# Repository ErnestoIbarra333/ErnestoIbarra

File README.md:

This are some of my school projects and personal projects :)

Metal_Friends: https://ernestoibarra333.github.io/projects/

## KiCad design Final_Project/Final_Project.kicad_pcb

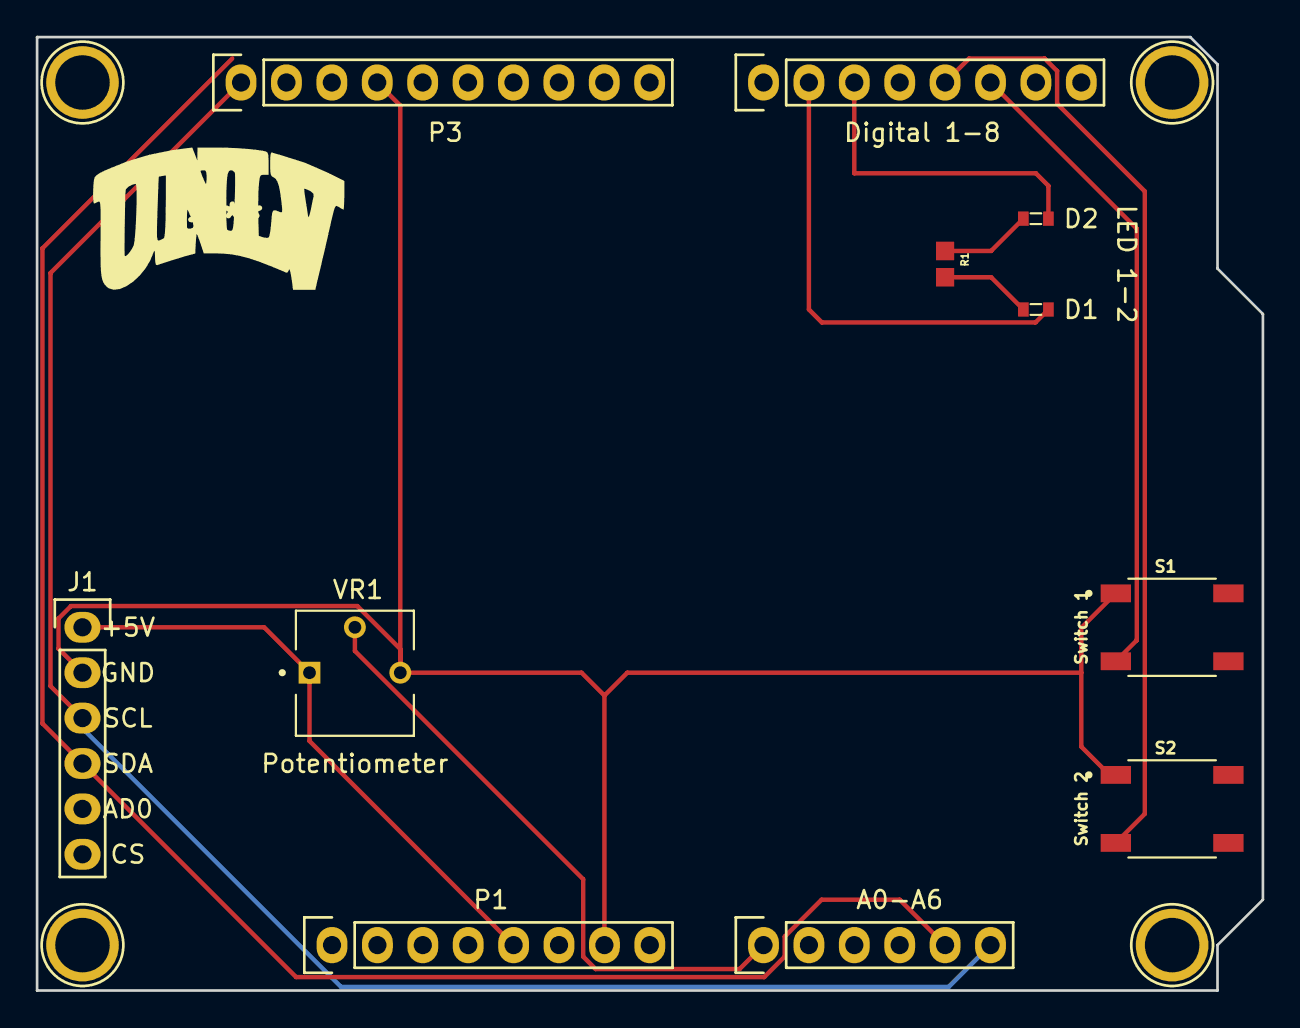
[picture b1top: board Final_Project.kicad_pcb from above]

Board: 2 copper layers, 68.6 x 53.3 mm, 15 parts (0 on the bottom side), 11 nets.

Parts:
A0-A6: Analog; Socket_Strip_Arduino_1x06
D1, D2: LTST-C193TBKT-5A; 0603
Digital 1-8: Digital; Socket_Strip_Arduino_1x08
J1: Conn_01x06_Female; Socket_Strip_Arduino_1x06
P1: Power; Socket_Strip_Arduino_1x08
P3: Digital; Socket_Strip_Arduino_1x10
P5, P6, P6#2, P8: CONN_01X01; Arduino_1pin
R1: RC0603JR-071KL; RESC1607X60N
S1, S2: 8-1437565-1; SW_8-1437565-1
VR1: 3362P-1-103LF; TRIM_3362P-1-103LF

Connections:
+5V: J1.1, P1.5, VR1.1
/2: Digital 1-8.6, S1.3
/3(**): Digital 1-8.5, S2.3
/5(**): D2.2, Digital 1-8.3
/6(**): D1.2, Digital 1-8.2
/A0: A0-A6.1, VR1.2
/A4(SDA): A0-A6.5, J1.4, P3.2
/A5(SCL): A0-A6.6, J1.3, P3.1
GND: J1.2, P1.6, P1.7, P3.4, S1.1, S2.1, VR1.3
unnamed: D1.1, R1.2
unnamed: D2.1, R1.1

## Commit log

2021-06-15 Testing
2021-06-15 class
2021-06-17 Midterms
2022-02-03 Create DA2
2022-02-06 delete
2022-11-10 Create LED Controller App
2023-09-09 adding test
2023-09-09 changing name
2023-09-09 Metal friends React App
